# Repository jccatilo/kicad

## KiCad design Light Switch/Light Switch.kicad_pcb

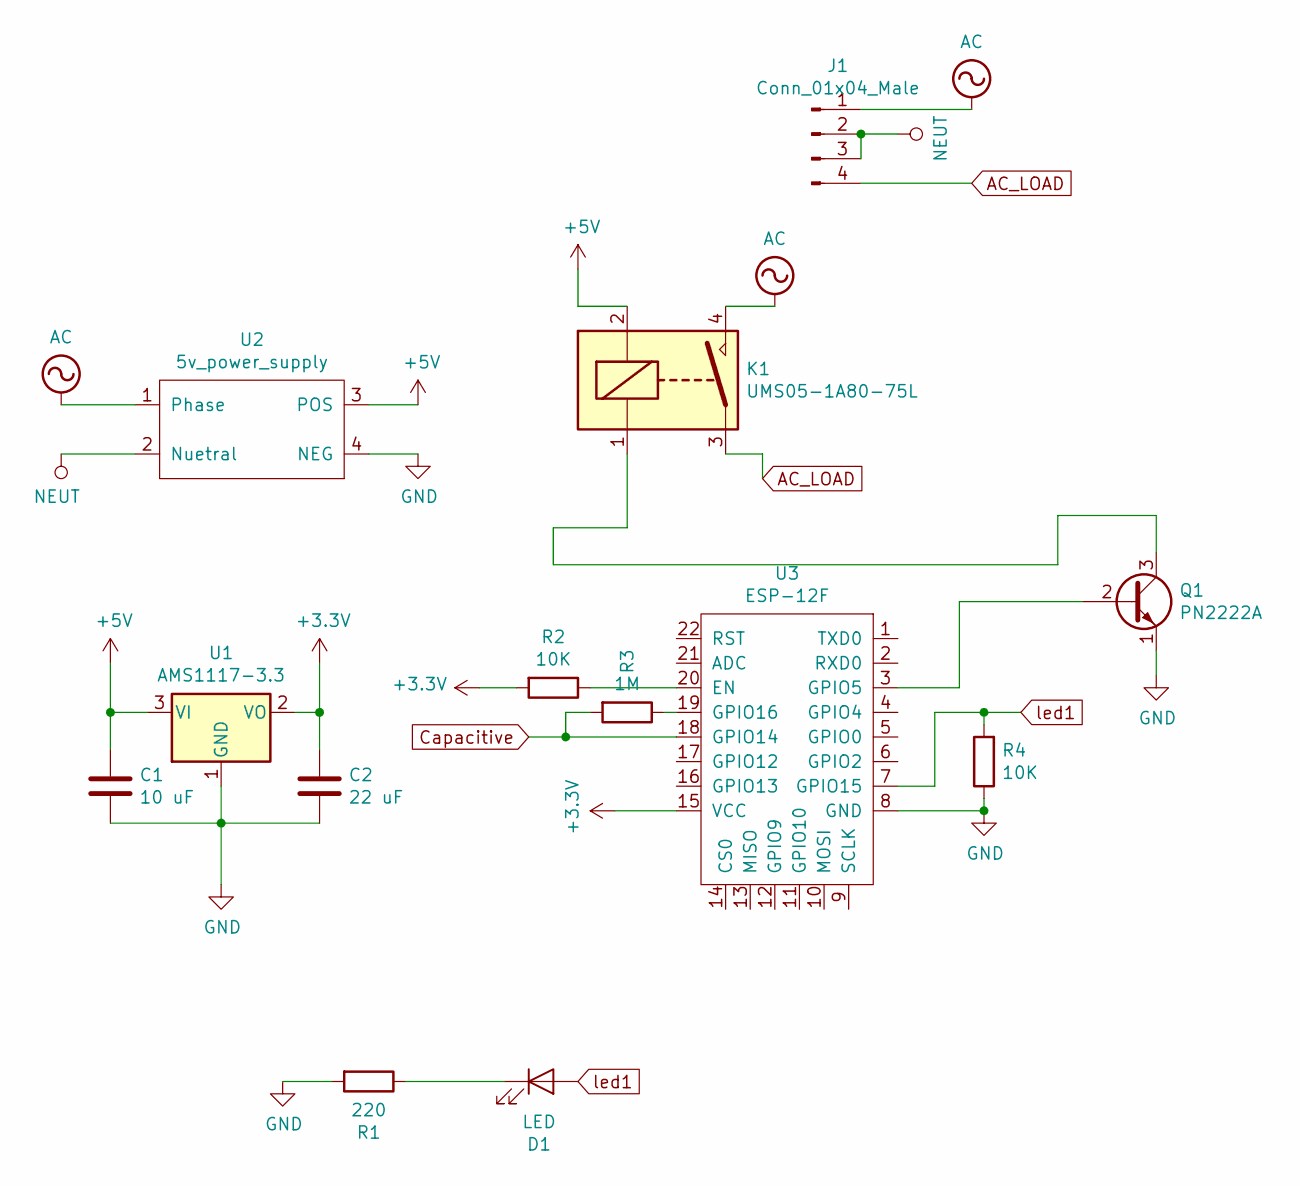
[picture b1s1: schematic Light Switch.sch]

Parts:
C1: 10 uF; C_0805_2012Metric_Pad1.15x1.40mm_HandSolder
C2: 22 uF; C_0805_2012Metric_Pad1.15x1.40mm_HandSolder
D1: LED; LED_0805_2012Metric_Pad1.15x1.40mm_HandSolder
J1: Conn_01x04_Male; Block_connector
K1: UMS05-1A80-75L; Solid_state_relay
Q1: PN2222A; SOT-23 2222A
R1: 220; C_0805_2012Metric_Pad1.15x1.40mm_HandSolder
R2, R4: 10K; C_0805_2012Metric_Pad1.15x1.40mm_HandSolder
R3: 1M; C_0805_2012Metric_Pad1.15x1.40mm_HandSolder
U1: AMS1117-3.3; SOT-223-3_TabPin2
U2: 5v_power_supply
U3: ESP-12F; esp-12

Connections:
+3V3: C2.1, R2.2, U1.2 (VO), U3.15 (VCC)
+5V: C1.1, K1.2, U1.3 (VI), U2.3 (POS)
AC: J1.1, K1.4, U2.1 (Phase)
AC_LOAD: J1.4, K1.3
Capacitive: R3.2, U3.18 (GPIO14)
GND: C1.2, C2.2, Q1.1 (E), R1.2, R4.1, U1.1 (GND), U2.4 (NEG), U3.8 (GND)
NEUT: J1.2, J1.3, U2.2 (Nuetral)
unnamed: D1.1 (K), R1.1
unnamed: K1.1, Q1.3 (C)
unnamed: Q1.2 (B), U3.3 (GPIO5)
unnamed: R2.1, U3.20 (EN)
unnamed: R3.1, U3.19 (GPIO16)
led1: D1.2 (A), R4.2, U3.7 (GPIO15)

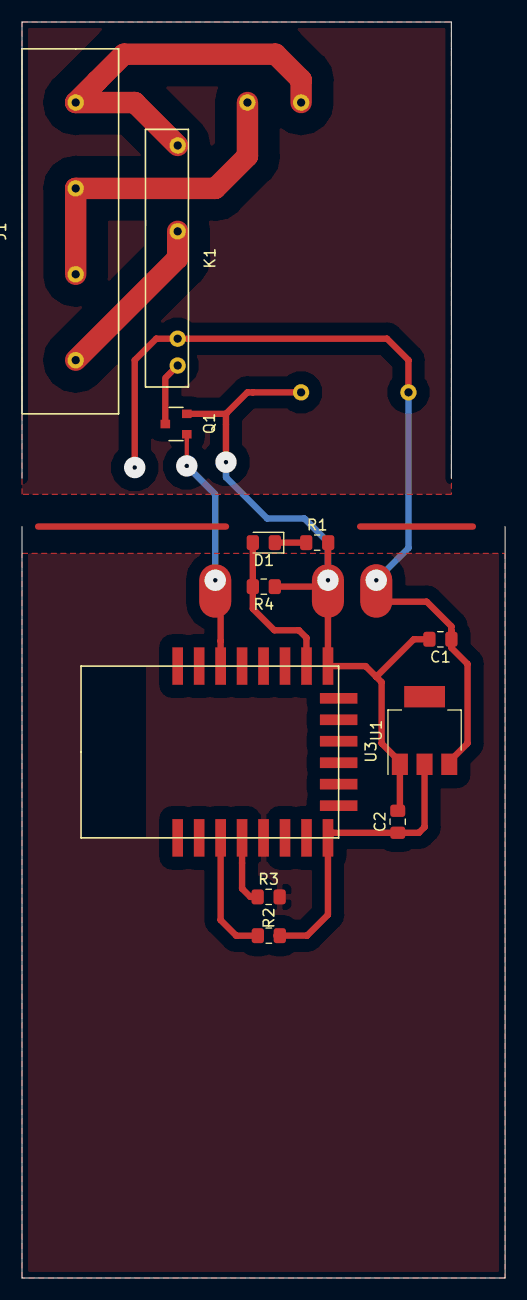
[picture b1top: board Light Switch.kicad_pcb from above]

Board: 2 copper layers, 45.0 x 117.0 mm, 13 parts (1 on the bottom side), 13 nets.

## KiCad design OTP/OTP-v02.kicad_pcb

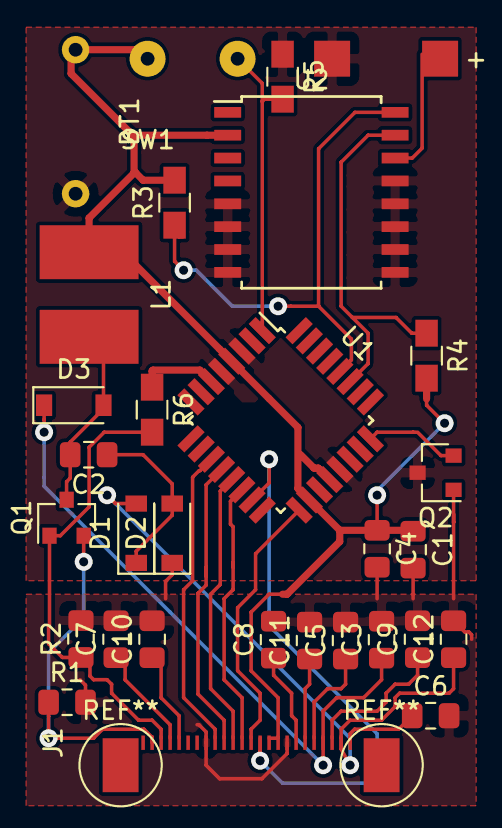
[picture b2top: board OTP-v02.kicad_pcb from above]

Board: 2 copper layers, 30 parts (0 on the bottom side), 27 nets.

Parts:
BT1: Battery 3V; Battery_pack_connector
BT2: Cell Battery 3V; Cell Battery SMD
C1, C2, C3: 4.7uF/50V; C_0805_2012Metric_Pad1.15x1.40mm_HandSolder
C4, C5, C6, C7, C8, C9, C10, C11, C12: 1uF/50V; C_0805_2012Metric_Pad1.15x1.40mm_HandSolder
D1, D2, D3: MBR0530; D_SOD-123
J1: FPC24
L1: 10uH 1A; CD54
Q1: 2N7000; SOT-23
Q2: PN2222A; SOT-23
R1, R2: R_US; R_0805_2012Metric_Pad1.15x1.40mm_HandSolder
R3, R4, R5, R6: R; C_0805_HandSoldering
SW1: Switch_SW_Push; pushbutton_2pin
U1: ATmega328P-AU; TQFP-32_7x7mm_P0.8mm
U2: DS3231M; SOIC-16W_7.5x10.3mm_P1.27mm

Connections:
BUSY: J1.9, U1.11
Batt: BT2.1, U2.14
CS: J1.12, U1.14
DC: J1.11, U1.13
GDR: J1.2, Q1.2, R1.1
GND: BT1.2, BT2.2, Q2.3, R5.1, U1.3, U1.5, U1.21, U2.5, U2.6, U2.7, U2.8, U2.9, U2.10, U2.11, U2.12, U2.13
unnamed: C2.1, D1.1, D2.2
unnamed: C2.2, D3.2, L1.2, Q1.3
unnamed: C5.1, J1.20
unnamed: C6.1, J1.24
unnamed: C7.1, J1.4
unnamed: C8.1, J1.18
unnamed: C9.1, J1.22
unnamed: C10.1, J1.5
unnamed: C11.1, J1.19
unnamed: Q2.2, U1.24
unnamed: R5.2, SW1.1, U1.1
PREVGH: C3.1, D3.1, J1.21
PREVGL: C12.1, D1.2, J1.23
QGND: C1.2, C3.2, C4.2, C5.2, C6.2, C7.2, C8.2, C9.2, C10.2, C11.2, C12.2, D2.1, J1.8, J1.17, Q2.1, R1.2, R2.2
RES: J1.10, U1.12
RESE: J1.3, Q1.1, R2.1, R6.2
SCL: R3.1, U1.28, U2.16
SCLK: J1.13, U1.17
SDA: R4.1, U1.27, U2.15
SDI: J1.14, U1.15
VDC: BT1.1, C1.1, C4.1, J1.15, J1.16, L1.1, R3.2, R4.2, R6.1, SW1.2, U1.4, U1.6, U1.18, U1.20, U2.2

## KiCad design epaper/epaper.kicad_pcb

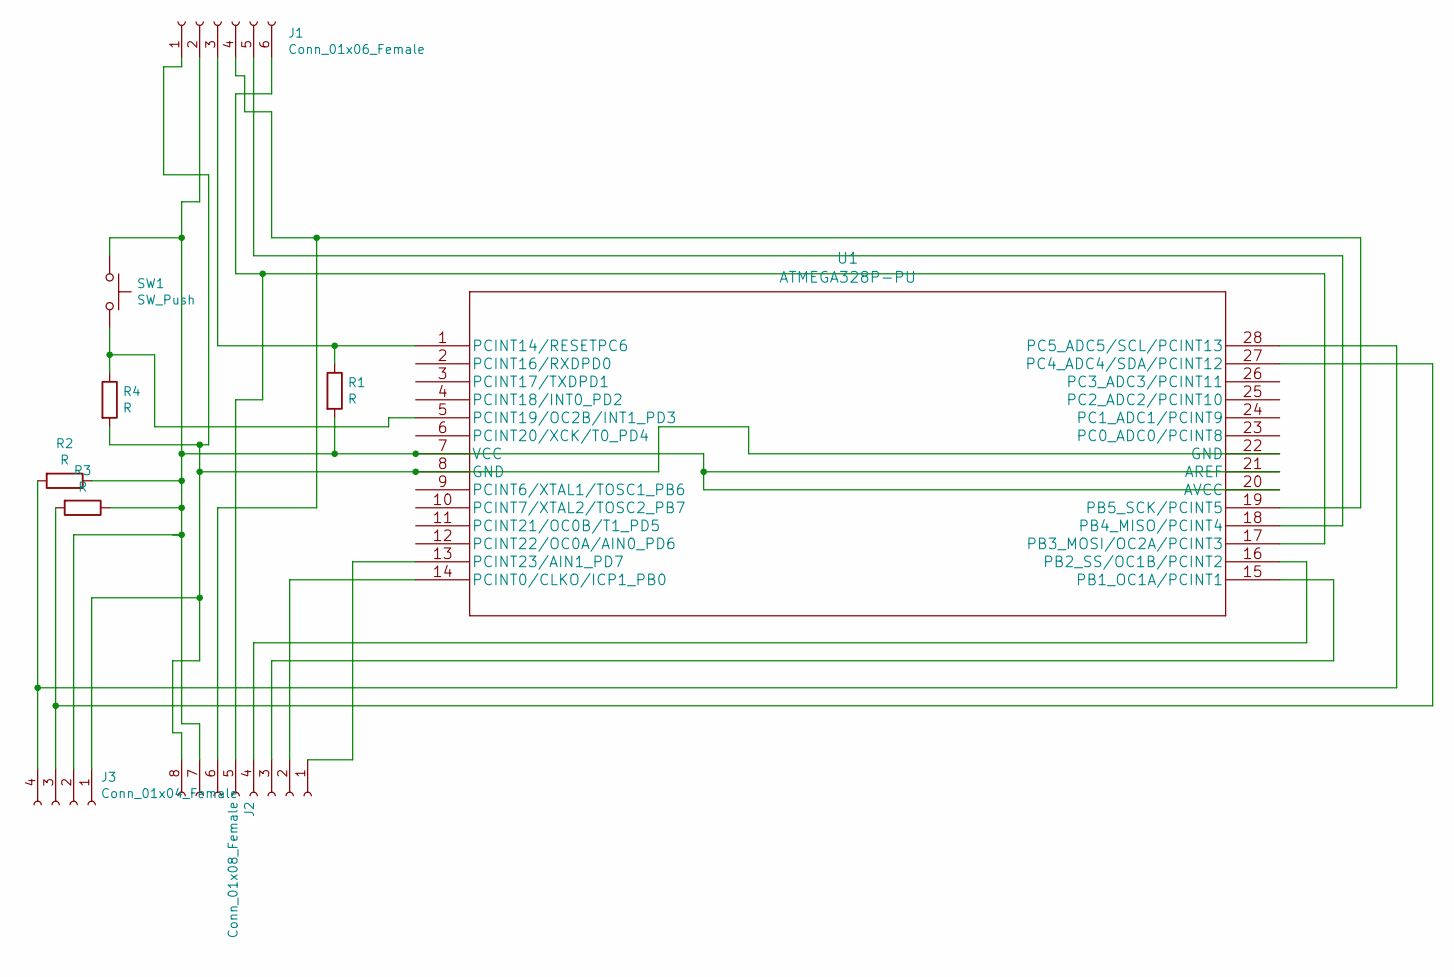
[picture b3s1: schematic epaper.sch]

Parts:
J1: Conn_01x06_Female; conn6
J2: Conn_01x08_Female; conn8
J3: Conn_01x04_Female; Connector4
R1, R2, R3, R4: R; C_0805_HandSoldering
SW1: SW_Push; pushbutton_2pin
U1: ATMEGA328P-PU

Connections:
unnamed: J1.1, J2.8, J3.1, R4.2, U1.8 (GND), U1.22 (GND)
unnamed: J1.2, J2.7, J3.2, R1.2, R2.1, R3.1, SW1.1, U1.7 (VCC), U1.20 (AVCC), U1.21 (AREF)
unnamed: J1.3, R1.1, U1.1 (PCINT14/RESETPC6)
unnamed: J1.4, J2.6, U1.19 (PB5_SCK/PCINT5)
unnamed: J1.5, U1.18 (PB4_MISO/PCINT4)
unnamed: J1.6, J2.5, U1.17 (PB3_MOSI/OC2A/PCINT3)
unnamed: J2.1, U1.13 (PCINT23/AIN1_PD7)
unnamed: J2.2, U1.14 (PCINT0/CLKO/ICP1_PB0)
unnamed: J2.3, U1.15 (PB1_OC1A/PCINT1)
unnamed: J2.4, U1.16 (PB2_SS/OC1B/PCINT2)
unnamed: J3.3, R3.2, U1.27 (PC4_ADC4/SDA/PCINT12)
unnamed: J3.4, R2.2, U1.28 (PC5_ADC5/SCL/PCINT13)
unnamed: R4.1, SW1.2, U1.5 (PCINT19/OC2B/INT1_PD3)

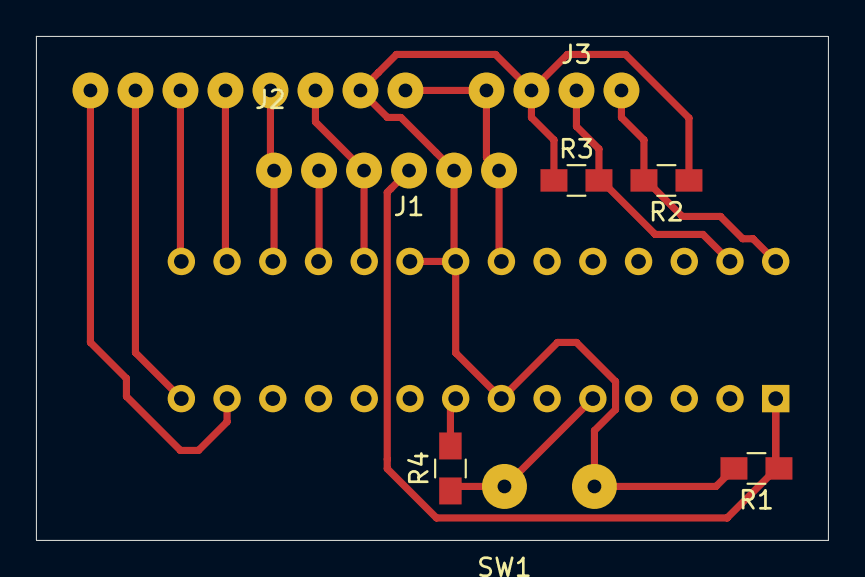
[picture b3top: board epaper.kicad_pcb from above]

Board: 2 copper layers, 44.0 x 28.0 mm, 9 parts (1 on the bottom side), 13 nets.

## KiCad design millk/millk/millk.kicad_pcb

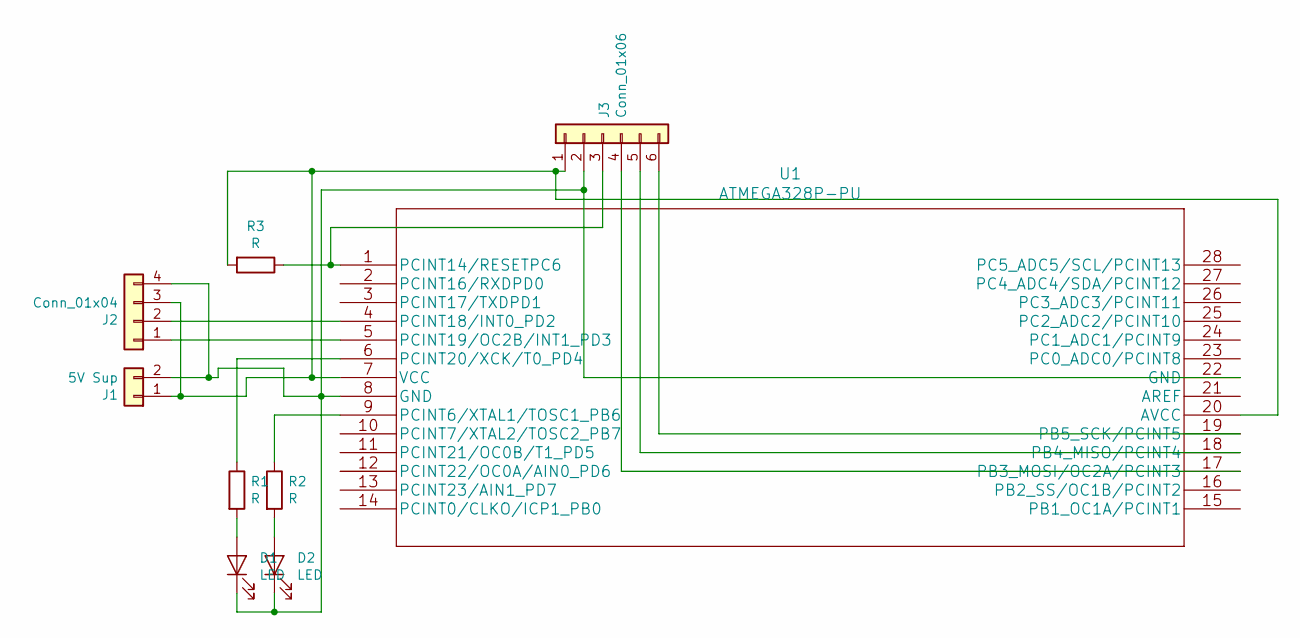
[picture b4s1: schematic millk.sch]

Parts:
D1, D2: LED; LED_D5.0mm
J1: 5V Sup; Conn2
J2: Conn_01x04; Connector4
J3: Conn_01x06; conn6
R1, R2, R3: R; R_Axial_DIN0207_L6.3mm_D2.5mm_P7.62mm_Horizontal
U1: ATMEGA328P-PU

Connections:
unnamed: D1.1 (K), D2.1 (K), J1.2, J2.4, J3.2, U1.8 (GND), U1.22 (GND)
unnamed: D1.2 (A), R1.2
unnamed: D2.2 (A), R2.2
unnamed: J1.1, J2.3, J3.1, R3.2, U1.7 (VCC), U1.20 (AVCC)
unnamed: J2.1, U1.5 (PCINT19/OC2B/INT1_PD3)
unnamed: J2.2, U1.4 (PCINT18/INT0_PD2)
unnamed: J3.3, R3.1, U1.1 (PCINT14/RESETPC6)
unnamed: J3.4, U1.17 (PB3_MOSI/OC2A/PCINT3)
unnamed: J3.5, U1.18 (PB4_MISO/PCINT4)
unnamed: J3.6, U1.19 (PB5_SCK/PCINT5)
unnamed: R1.1, U1.6 (PCINT20/XCK/T0_PD4)
unnamed: R2.1, U1.9 (PCINT6/XTAL1/TOSC1_PB6)

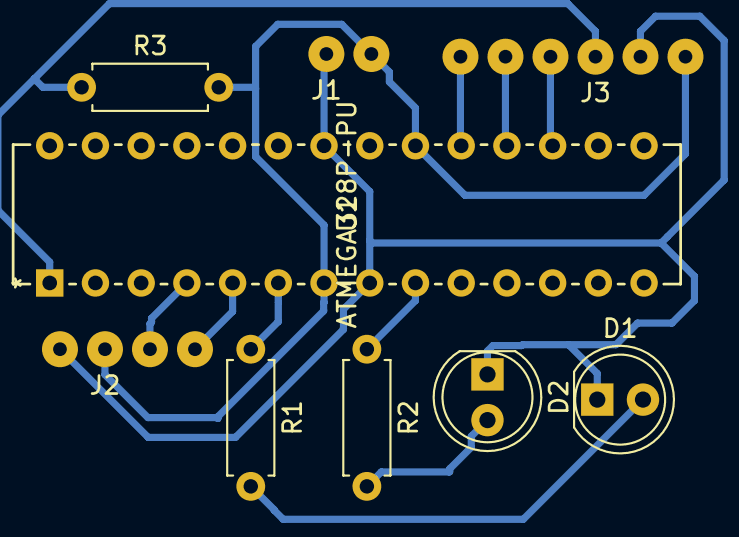
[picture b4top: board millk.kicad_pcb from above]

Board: 2 copper layers, 9 parts (0 on the bottom side), 12 nets.

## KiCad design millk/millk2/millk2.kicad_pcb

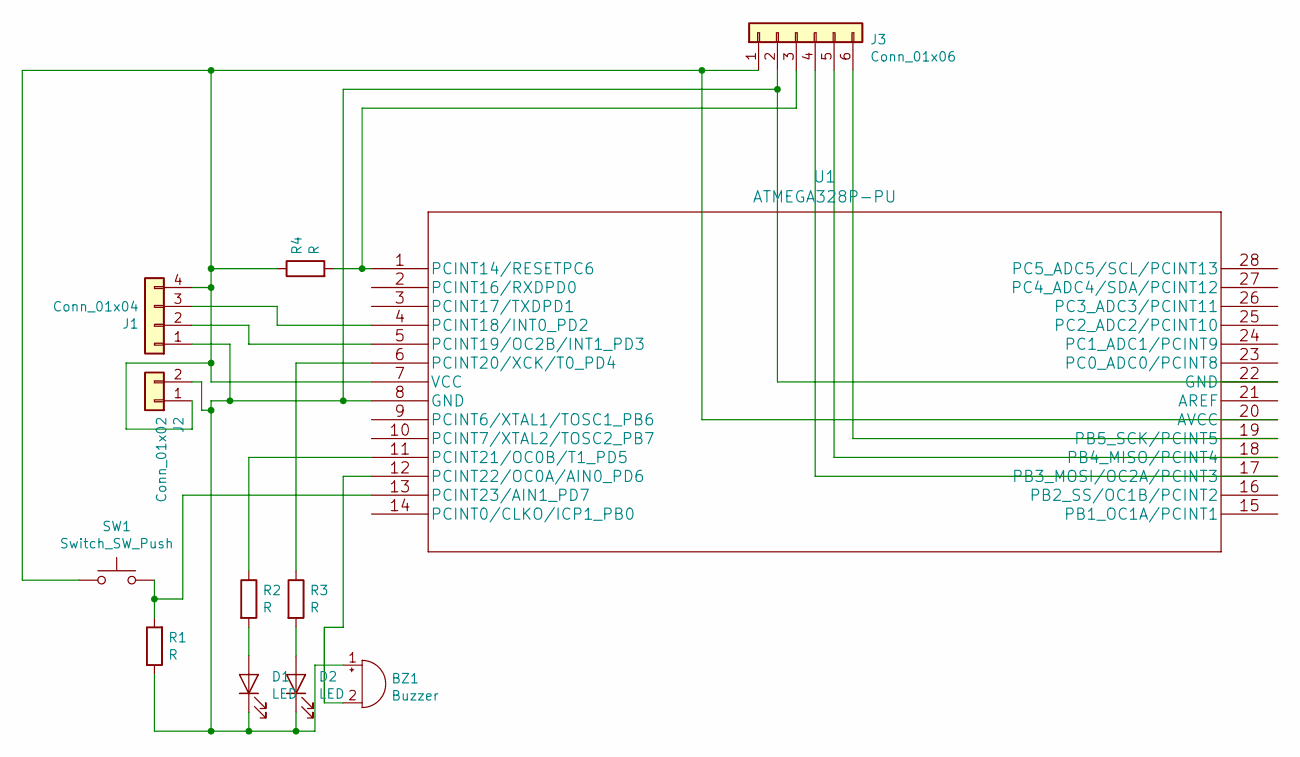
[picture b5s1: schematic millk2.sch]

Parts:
BZ1: Buzzer; LED_D5.0mm
D1, D2: LED; LED_D5.0mm
J1: Conn_01x04; Connector4
J2: Conn_01x02; Conn2
J3: Conn_01x06; conn6
R1, R2, R3, R4: R; C_0805
SW1: Switch_SW_Push; LED_D5.0mm
U1: ATMEGA328P-PU

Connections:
unnamed: BZ1.1 (-), D1.1 (K), D2.1 (K), J1.1, J2.2, J3.2, R1.1, U1.8 (GND), U1.22 (GND)
unnamed: BZ1.2 (+), U1.12 (PCINT22/OC0A/AIN0_PD6)
unnamed: D1.2 (A), R2.2
unnamed: D2.2 (A), R3.2
unnamed: J1.2, U1.5 (PCINT19/OC2B/INT1_PD3)
unnamed: J1.3, U1.4 (PCINT18/INT0_PD2)
unnamed: J1.4, J2.1, J3.1, R4.1, SW1.1, U1.7 (VCC), U1.20 (AVCC)
unnamed: J3.3, R4.2, U1.1 (PCINT14/RESETPC6)
unnamed: J3.4, U1.17 (PB3_MOSI/OC2A/PCINT3)
unnamed: J3.5, U1.18 (PB4_MISO/PCINT4)
unnamed: J3.6, U1.19 (PB5_SCK/PCINT5)
unnamed: R1.2, SW1.2, U1.13 (PCINT23/AIN1_PD7)
unnamed: R2.1, U1.11 (PCINT21/OC0B/T1_PD5)
unnamed: R3.1, U1.6 (PCINT20/XCK/T0_PD4)

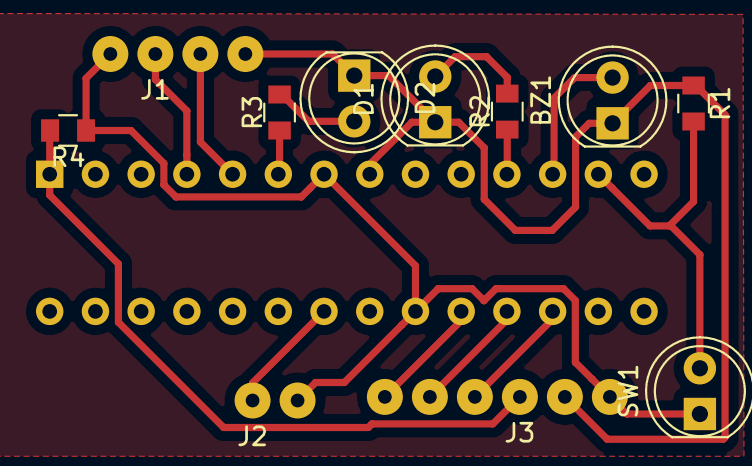
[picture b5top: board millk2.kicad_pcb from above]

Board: 2 copper layers, 12 parts (1 on the bottom side), 14 nets.

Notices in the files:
parts and their libraries:
Copyright 2016 Accelerated Designs. All rights reserved.
